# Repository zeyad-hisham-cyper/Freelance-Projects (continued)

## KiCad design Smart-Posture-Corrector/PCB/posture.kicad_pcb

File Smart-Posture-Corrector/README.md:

# Smart Posture Corrector — "Second Spine"

**A two-board wearable that watches your back and neck angle with two IMUs, buzzes you when you slouch, and streams live posture data to a Flutter companion app over Bluetooth Low Energy.**

ESP32 · 2× MPU-6050 · complementary filter · haptic feedback · BLE GATT · Flutter · KiCad 9 · 1S Li-Po with TP4056 charging and MT3608 boost

---

## Overview

The project began with a client specification (`Smart Posture Corrector.docx`) for a wearable aimed at **doctors and dentists**. These users spend long hours in strained working postures. The device needed to:

- monitor the **upper back (thoracic)** and **neck (cervical)** separately, and interpret the neck *relative to* the back ("sensor coherence")
- give a **gentle, location-specific vibration** when posture leaves the calibrated envelope
- **calibrate** to the user's normal working posture, then **tighten the threshold progressively** (adaptive correction, e.g. 30° → 25° → 20°)
- provide a **Special mode** for procedures that need an awkward posture. This mode mutes alerts but still gives a periodic "take a break" reminder.
- be controllable from a **button on the device** and from a **companion mobile app**

This repository contains the full implementation:

| Part | Folder | What it is |
|---|---|---|
| Firmware | [`main/posture controller/`](main/posture%20controller/) | PlatformIO / Arduino-ESP32 firmware (modular C++) |
| Mobile app | [`second_spine/`](second_spine/) | Flutter app "Second Spine" (BLE dashboard, controls, history) |
| Hardware | [`PCB/`](PCB/) | KiCad 9 project: Back board (main) + Neck board, plus Gerbers |
| Docs | [`docs/`](docs/) | Exported schematics (PDF/SVG), PCB layout and 3D renders |

> The device is a wellness and ergonomics aid for healthy users, not a medical device. The original specification says the same.

---

## Features

**Device / firmware**
- Two MPU-6050 IMUs on one I²C bus at 400 kHz: **back sensor at `0x68`**, **neck sensor at `0x69`**
- Pitch is estimated at **100 Hz** with a **complementary filter** (α = 0.96, gyro ±250 °/s)
- The neck angle is reported **relative to the back** (`neck − back`), so leaning the whole torso is not counted as a neck fault
- **Calibration** averages the user's posture over 2 minutes. The baseline and sensitivity level are stored in flash (EEPROM emulation) and survive power cycles.
- **6 sensitivity levels (0–5).** Each level tightens the threshold by 5°, with floors of 15° (back) and 10° (neck).
- **Two-stage, location-specific haptics:** a double buzz after 3 s of bad posture and a triple buzz after 15 s. Only the offending zone's motor (back or neck) vibrates.
- **Special mode:** posture alerts are muted and both motors give a short reminder buzz every 5 minutes
- **One-button UI:** a short press toggles Special mode and a long press (≥ 1.5 s) re-calibrates
- **BLE GATT server** (`PostureCorrector`): JSON telemetry at about 5 Hz plus a text command channel. Advertising restarts automatically after a disconnect.
- A serial debug console accepts single-key commands

**Companion app (Second Spine)**
- BLE scan and connect with Android 12+ runtime permissions
- Live dashboard: Good/Bad status, back and neck arc gauges against their thresholds, and per-zone hints
- Remote **Calibrate**, **Normal ↔ Special** toggle and **sensitivity slider**. The level is saved locally and re-sent on every connect.
- History screen with a posture-trend chart (fl_chart) and session cards (see the [status](#roadmap--status) note below)
- Dark "glass" UI theme using the Outfit font (Google Fonts), locked to portrait

**Hardware**
- Two custom PCBs connected by a 6-wire cable (3V3, GND, SCL, SDA, neck-motor drive, battery rail)
- 1S Li-Po → TP4056 charger module → slide power switch → MT3608 boost (5 V) → ESP32-DevKitC (on-board 3V3 LDO)
- Coin vibration motors on low-side NPN drivers with flyback diodes
- Through-hole (THT) design routed on the bottom copper layer only (see [PCB manufacturing](#pcb-manufacturing))

---

## System architecture

```mermaid
flowchart LR
    subgraph NECK["Neck board"]
        IMU2["GY-521<br/>MPU-6050 @0x69"]
        DRV2["NPN driver<br/>+ flyback diode"]
        M2(("Neck<br/>coin motor"))
        DRV2 --> M2
    end

    subgraph BACK["Back board (main)"]
        IMU1["GY-87<br/>MPU-6050 @0x68"]
        ESP["ESP32-DevKitC-32E<br/>PostureApp firmware"]
        BTN["Push button<br/>GPIO16"]
        DRV1["NPN driver<br/>+ flyback diode"]
        M1(("Back<br/>coin motor"))
        PWR["1S Li-Po → TP4056<br/>→ switch → MT3608 5 V"]
        DRV1 --> M1
    end

    IMU1 -- "I²C 400 kHz" --> ESP
    IMU2 -- "I²C over 6-pin JST cable" --> ESP
    BTN --> ESP
    ESP -- "GPIO25 (VM2)" --> DRV1
    ESP -- "GPIO17 (VM1) over cable" --> DRV2
    PWR -- "5 V → DevKit LDO → 3V3" --> ESP

    ESP <-- "BLE GATT<br/>JSON notify @5 Hz / text commands" --> APP["📱 Second Spine<br/>Flutter app"]
    APP --> SP[("SharedPreferences<br/>level · device id · sessions")]
```

Data flow: **IMUs → complementary filter → back angle and neck-relative angle → threshold logic → vibration events**. In parallel, **angles, thresholds and mode → JSON → BLE notify → app UI**.

---

## Hardware

Two boards share one KiCad project (`PCB/posture.kicad_pro`). The v2 layout places both outlines on one panel. The silkscreen reads *"Back Board"*, *"Smart Posture V 0.3"* and *"Second Spine"*.

| Board | Outline (from `posture.kicad_pcb`) | Contents |
|---|---|---|
| **Back board (main)** | ≈ 98 × 65 mm | ESP32-DevKitC-32E, GY-87 IMU (back sensor), TP4056 and MT3608 module footprints, Li-Po JST, slide switch, push button, back motor driver and JST, 6-pin cable connector, bulk capacitors |
| **Neck board** | ≈ 31 × 44 mm | GY-521 IMU (neck sensor, AD0 pulled up → `0x69`), neck motor driver and JST, 6-pin cable connector |

There is also a standalone neck schematic at `PCB/neck/neck.kicad_sch` with the same circuit. No separate `neck.kicad_pcb` file exists in the repo. The neck layout lives in the combined `posture.kicad_pcb`, and the older standalone neck board survives only as Gerbers (`PCB/Board2/`).

### BOM highlights (from the schematic)

| Ref | Part | Role |
|---|---|---|
| U1 | ESP32-DevKitC-32E (module footprint) | MCU, BLE radio, USB programming |
| U3 | GY-87 10-DOF breakout (MPU-6050 + extras) | Back IMU, `0x68`. Only the MPU-6050 is used by the firmware. |
| U2 | GY-521 breakout (MPU-6050) | Neck IMU, `0x69` (R3 4.7 kΩ pulls AD0 to 3V3) |
| — | TP4056 module (J3/J11 headers) | 1S Li-Po charging (B+/B−, OUT+/OUT−) |
| — | MT3608 module (J5–J8 pins) | Boost converter, battery → +5 V for the DevKit |
| SW2 | SPDT slide switch | Main power (TP4056 OUT+ → MT3608 VIN+) |
| SW1 | Tactile push button | Mode / calibrate (GPIO16, internal pull-up) |
| Q1, Q2 | NPN BJT, TO-92 | Low-side vibration-motor switches |
| R2, R4 / R1, R5 | 470 Ω / 10 kΩ | Base resistor / base pull-down |
| D1, D3 | 1N4001 | Motor flyback diodes |
| J4, J10 | 2-pin JST | Coin vibration motors (neck / back) |
| J9 | 2-pin JST | 1S Li-Po battery |
| J1, J2 | 6-pin JST (locking) | Back ↔ Neck board cable |
| C3, C4 | 100 nF + 10 µF | +5 V decoupling |

Third-party symbols, footprints and 3D models (GY-521, GY-87, a C0720B001F coin-motor footprint) are in `PCB/lib/` and `PCB/GY-521.pretty/`. They were downloaded from SnapEDA.

### Pin map (ESP32-DevKitC-32E)

| Signal | GPIO | Net | Notes |
|---|---|---|---|
| I²C SDA | 21 | `SDA` | Shared by both IMUs and routed to the neck board |
| I²C SCL | 22 | `SCL` | 400 kHz |
| Back motor | 25 | `VM2` | Q1 → J10 (back board) |
| Neck motor | 17 | `VM1` | Sent over the cable → neck-board driver → neck motor |
| Button | 16 | `IO16` | Active-low, `INPUT_PULLUP`, 40 ms debounce |
| 5 V in | 5V pin | `+5V` | From MT3608 |
| 3V3 | 3V3 pin | `+3.3V` | DevKit LDO output → IMUs |

The firmware pins (`src/PostureApp.cpp`) match the v2 netlist.

**Inter-board cable (J1/J2, 6-pin):** `1 +3.3V · 2 GND · 3 SCL · 4 SDA · 5 VM1 · 6 3.7V`

### Power path

```
1S Li-Po (J9) ──► TP4056 module (charge + B−) ──OUT+──► SW2 ──► MT3608 boost ──► +5V ──► ESP32-DevKitC 5V pin
      │                                                                                     └─ on-board LDO ─► +3.3V ─► IMUs
      └──── "3.7V" rail (battery +) ──► coin motors (high side) ◄── NPN low-side switch ◄── GPIO
```

Inference from the netlist: the motors run directly from the battery rail and are switched on the low side. They draw nothing while the ESP32 is off, because the transistors are held off by the 10 kΩ base pull-downs. The design does not include battery-voltage sensing.

Schematics: [main board PDF](docs/main_board_schematic.pdf) · [neck board PDF](docs/neck_board_schematic.pdf)

---

## Firmware

PlatformIO project, `env:esp32dev` (Arduino framework, `espressif32`), 115200 baud monitor, 921600 baud upload.

### Module structure

```
posture controller/
├── src/main.cpp              → setup()/loop(), creates PostureApp
├── src/PostureApp.cpp        → app state machine, pins, button/serial/BLE wiring
├── include/PostureApp.h
├── lib/Sensors/              → raw MPU-6050 I²C reads + complementary filter
├── lib/PostureLogic/         → calibration, thresholds, bad-posture timing, EEPROM persistence
├── lib/Hardware/button.*     → debounced short/long press detector
├── lib/Hardware/vibrationCoin.* → non-blocking vibration patterns
├── lib/BLEDashboard/         → BLE GATT server (ESP32 BLE Arduino)
└── test/test_logic.cpp       → Unity tests for PostureLogic (see status)
```

Everything is **non-blocking** and driven by `millis()`. The main loop updates the button, sensors, motors and BLE every iteration.

### Posture algorithm

1. **Sensing (100 Hz).** For each MPU-6050, read 14 bytes from `0x3B`.
   - Accelerometer pitch: `atan2(−ax, √(ay² + az²))`
   - Gyro rate: `gy / 131` °/s
   - Fusion: `angle = 0.96·(angle + gyro·dt) + 0.04·accel_pitch`
2. **Neck coherence.** `neckRel = neckAngle − backAngle`
3. **Calibration (2 min).** The firmware averages `back` and `neckRel` to get the baseline, resets the level to 0 and saves the result to flash. The firmware comment marks the 2-minute duration as "for testing". The spec suggests 15–30 min or longer.
4. **Threshold.** `th = baseline − 5° × level`, clamped to **≥ 15° (back)** and **≥ 10° (neck)**.
5. **Detection.** Posture is bad when `|back| > backTh` **or** `|neckRel| > neckTh`.
   - Bad for 3 s → `FIRST_BAD` → double buzz
   - Bad for 15 s → `PERSISTENT_BAD` → triple buzz
   - Further alerts stop until posture recovers
   - Only the motor for the offending zone fires

**Flash layout (64-byte EEPROM emulation):** magic `0x504F5354` ("POST") @0, level @4, baseline back (float) @8, baseline neck (float) @12.

### State machine

```mermaid
stateDiagram-v2
    [*] --> CALIBRATING: no valid baseline in flash
    [*] --> NORMAL: baseline loaded
    CALIBRATING --> NORMAL: 2 min elapsed → save baseline, triple buzz (both motors)
    NORMAL --> SPECIAL: short press / TOGGLE_MODE (double buzz)
    SPECIAL --> NORMAL: short press / TOGGLE_MODE (short buzz)
    NORMAL --> CALIBRATING: long press ≥1.5 s / CALIBRATE
    SPECIAL --> CALIBRATING: long press ≥1.5 s / CALIBRATE
    CALIBRATING --> CALIBRATING: long press / CALIBRATE (restart)

    state NORMAL {
        [*] --> Good
        Good --> Bad: angle > threshold
        Bad --> Good: posture corrected
        Bad --> Warned: 3 s → double buzz
        Warned --> Persistent: 15 s → triple buzz
        Warned --> Good
        Persistent --> Good
    }
    note right of SPECIAL: alerts muted, short reminder buzz every 5 min
```

### Vibration patterns

| Pattern | Timing | Used for |
|---|---|---|
| Short | 200 ms | Leaving Special mode, 5-min Special reminder |
| Double | 2 × (200 ms on / 150 ms off) | Entering Special mode, first bad-posture warning |
| Triple | 3 × (200 ms on / 150 ms off) | Calibration done, persistent bad posture |

### BLE protocol

Device name **`PostureCorrector`**. The service UUID is advertised with a scan response enabled.

| Item | UUID | Properties | Payload |
|---|---|---|---|
| Service | `12345678-1234-1234-1234-123456789abc` | — | — |
| Posture data | `12345678-1234-1234-1234-000000000001` | Read, Notify | JSON, about every 200 ms while connected |
| Command | `12345678-1234-1234-1234-000000000002` | Write | UTF-8 text command |
| Status | `12345678-1234-1234-1234-000000000003` | Read | `"CALIBRATING"` / `"NORMAL"` / `"SPECIAL"` |

**Notify payload:**

```json
{"back":12.50,"neck":-3.20,"backTh":15.0,"neckTh":10.0,"mode":1,"calibrating":false}
```

`mode`: `0` Calibrating, `1` Normal, `2` Special. `back` is in degrees and `neck` is the neck-relative angle.

**Commands:**

| Command | Effect |
|---|---|
| `CALIBRATE` | Start a 2-minute calibration |
| `TOGGLE_MODE` | Normal ↔ Special (ignored while calibrating) |
| `LEVEL:n` | Set sensitivity level `n` = 0–5 (values above 5 are clamped). Saved to flash. |

**Serial console (115200 baud):** `c` calibrate · `s` toggle Special · `n` force Normal · `0`–`5` set level. The device prints `[APP] Mode=… | Back=… | Neck=…` once per second.

---

## Mobile app — Second Spine

Flutter (Dart SDK `^3.10.4`), dark theme, portrait only. It has three tabs:

| Tab | Screen | What it does |
|---|---|---|
| Dashboard | `home_screen.dart` | Connection chip, Good/Bad status card (pulses when bad), calibrating spinner, back and neck `AngleGauge`s, Calibrate and Mode buttons, sensitivity slider (0–5) with live `±backTh / ±neckTh` |
| Connect | `connect_screen.dart` | Radar-style 15 s BLE scan, device list with RSSI, connect/disconnect. On connect it stores the device id and re-sends the saved `LEVEL:n`. |
| History | `history_screen.dart` | Posture-trend line chart (last 10 sessions) and session cards (duration, % good posture, Good ≥ 70 %) |

**Architecture:** `BleService` (a `ChangeNotifier` around `flutter_blue_plus` that exposes a `PostureData` stream) and `StorageService` (`shared_preferences` keys `sensitivity_level`, `last_device_id`, `session_history`, keeping at most 50 sessions).

**Packages** (`pubspec.yaml`): `flutter_blue_plus ^1.35.5`, `permission_handler ^12.0.1`, `shared_preferences ^2.3.4`, `fl_chart ^0.70.2`, `google_fonts ^6.2.1`, `cupertino_icons`. Dev: `flutter_lints ^6.0.0`.

See [`second_spine/README.md`](second_spine/README.md) for details.

---

## Build & flash the firmware

Requires [PlatformIO](https://platformio.org/) (CLI or the VS Code extension).

```bash
cd "main/posture controller"
pio run                         # build
pio run -t upload               # flash the ESP32-DevKitC over USB
pio device monitor -b 115200    # serial console (c / s / n / 0-5)
```

On first boot the device has no baseline, so it **starts calibrating immediately**. Sit or stand in your normal working posture for 2 minutes and wait for the triple buzz.

## Run the app

```bash
cd second_spine
flutter pub get
flutter run            # with an Android phone connected (BLE needs a real device)
flutter build apk      # release APK (currently signed with the debug key)
```

Android permissions (`BLUETOOTH_SCAN`, `BLUETOOTH_CONNECT`, and location on Android ≤ 11) are already declared in `AndroidManifest.xml`. iOS has not been configured yet; see the status section.

---

## PCB manufacturing

The design is KiCad 9 (`PCB/posture.kicad_pro`), 1.6 mm FR-4. All tracks (0.5 / 0.8 / 1.0 mm) are on **B.Cu** with a GND pour, and every part is through-hole. Each Gerber set exports bottom copper only (there is no `F_Cu.gbr`). That suits single-sided or home/CNC fabrication, and a fab house can also build it as a 2-layer board with an empty top layer.

| Folder | Date (job file) | Board size | Contents | Status |
|---|---|---|---|---|
| `PCB/Board1/` (+ `Board1.zip`) | 2026-01-13 | 103.8 × 61.9 mm | First back board. No on-board Li-Po JST, power switch or bulk caps; button net differs. | Superseded |
| `PCB/Board2/` (+ `Board2.zip`) | 2026-01-13 | 44.4 × 33.1 mm | First standalone neck board | Superseded |
| **`PCB/v2/`** (+ `v2/v2.zip`) | **2026-03-16** | **133.6 × 65.4 mm panel** | **Back board + neck board on one panel**. Adds Li-Po JST, SW2 power switch, 5 V decoupling and button on GPIO16, and matches the current firmware pin map. | **Current** |

Gerbers were generated with Pcbnew 9.0.2. For ordering, upload `PCB/v2/v2.zip`. It contains two separate outlines, so ask the fab to route or separate them, or order them as a panel.

---

## Gallery

| | |
|---|---|
|  |  |
| 3D render, top | 3D render, bottom (single-sided routing + GND pour) |

**PCB layout:** [`docs/images/main_board/pcb_layout.svg`](docs/images/main_board/pcb_layout.svg)

**Schematics**

| Sheet | File |
|---|---|
| Main board (root) | [`posture.svg`](docs/images/main_board/schematic/posture.svg) |
| TP4056 charger sheet | [`posture-TP4056.svg`](docs/images/main_board/schematic/posture-TP4056.svg) |
| MT3608 boost sheet | [`posture-MT3608.svg`](docs/images/main_board/schematic/posture-MT3608.svg) |
| Neck board | [`neck.svg`](docs/images/neck_board/schematic/neck.svg) |

---

## Repository structure

```
Smart-Posture-Corrector/
├── README.md                         ← you are here
├── Smart Posture Corrector.docx      ← original client specification
├── docs/
│   ├── main_board_schematic.pdf
│   ├── neck_board_schematic.pdf
│   └── images/
│       ├── main_board/   pcb_3d_iso/top/bottom.png, pcb_layout.svg, schematic/*.svg
│       └── neck_board/   schematic/neck.svg
├── main/                             ← firmware repo
│   ├── README.md
│   └── posture controller/           ← PlatformIO project
│       ├── platformio.ini
│       ├── include/  src/  lib/  test/
│       └── README.md                 ← BLE integration guide
├── second_spine/                     ← Flutter companion app
│   ├── pubspec.yaml
│   ├── lib/ (main.dart, models/, screens/, services/, theme/, widgets/)
│   ├── android/ ios/ web/ windows/ linux/ macos/
│   └── README.md
└── PCB/                              ← KiCad 9 project
    ├── posture.kicad_pro/.kicad_sch/.kicad_pcb   (main + neck panel)
    ├── TP4056.kicad_sch  MT3608.kicad_sch        (hierarchical sheets)
    ├── neck/neck.kicad_sch                       (standalone neck schematic)
    ├── GY-521.pretty/  lib/                      (third-party parts, SnapEDA)
    ├── Board1/  Board2/                          (v1 Gerbers)
    └── v2/                                       (current Gerbers)
```

---

## Roadmap / status

Status (from the files): the firmware, BLE protocol, app and v2 PCB are complete and consistent with each other. The items below are open or differ from the original spec.

- [ ] **Automatic weekly threshold tightening.** The level (0–5) is currently set manually from the app or serial console. The spec asks for automatic weekly progression.
- [ ] **Special-mode auto-timeout.** The spec suggests about 30 min. Today Special mode lasts until it is toggled off.
- [ ] **Production calibration time.** Calibration is 2 min (marked "for testing"). It also needs a stillness/validity check.
- [ ] **Session history.** `StorageService.addSession()` exists, but nothing records sessions yet, so the History tab stays empty.
- [ ] **Auto-reconnect.** `last_device_id` is saved but not yet used.
- [ ] **iOS.** `NSBluetoothAlwaysUsageDescription` must be added to `Info.plist` before BLE works on iOS.
- [ ] **Unit tests.** `test/test_logic.cpp` accesses private members, and its expected threshold ignores the 15° floor, so it needs updating before `pio test` passes.
- [ ] **Portability.** Some includes differ in case from the file names (`"Sensors.h"`, `"PostureLogic.h"`). This builds on Windows but will fail on Linux/macOS CI. The `Adafruit MPU6050` dependency and the `I2C_SDA/SCL` build flags are declared but unused.
- [ ] **Hardware ideas.** Battery-voltage sense, the GY-87 magnetometer/barometer (currently unused), and an enclosure / strap mount.

---

**Author:** [@zeyad-hisham-cyper](https://github.com/zeyad-hisham-cyper) — Embedded Systems & PCB Design · Part of the [Freelance Projects](../README.md) portfolio

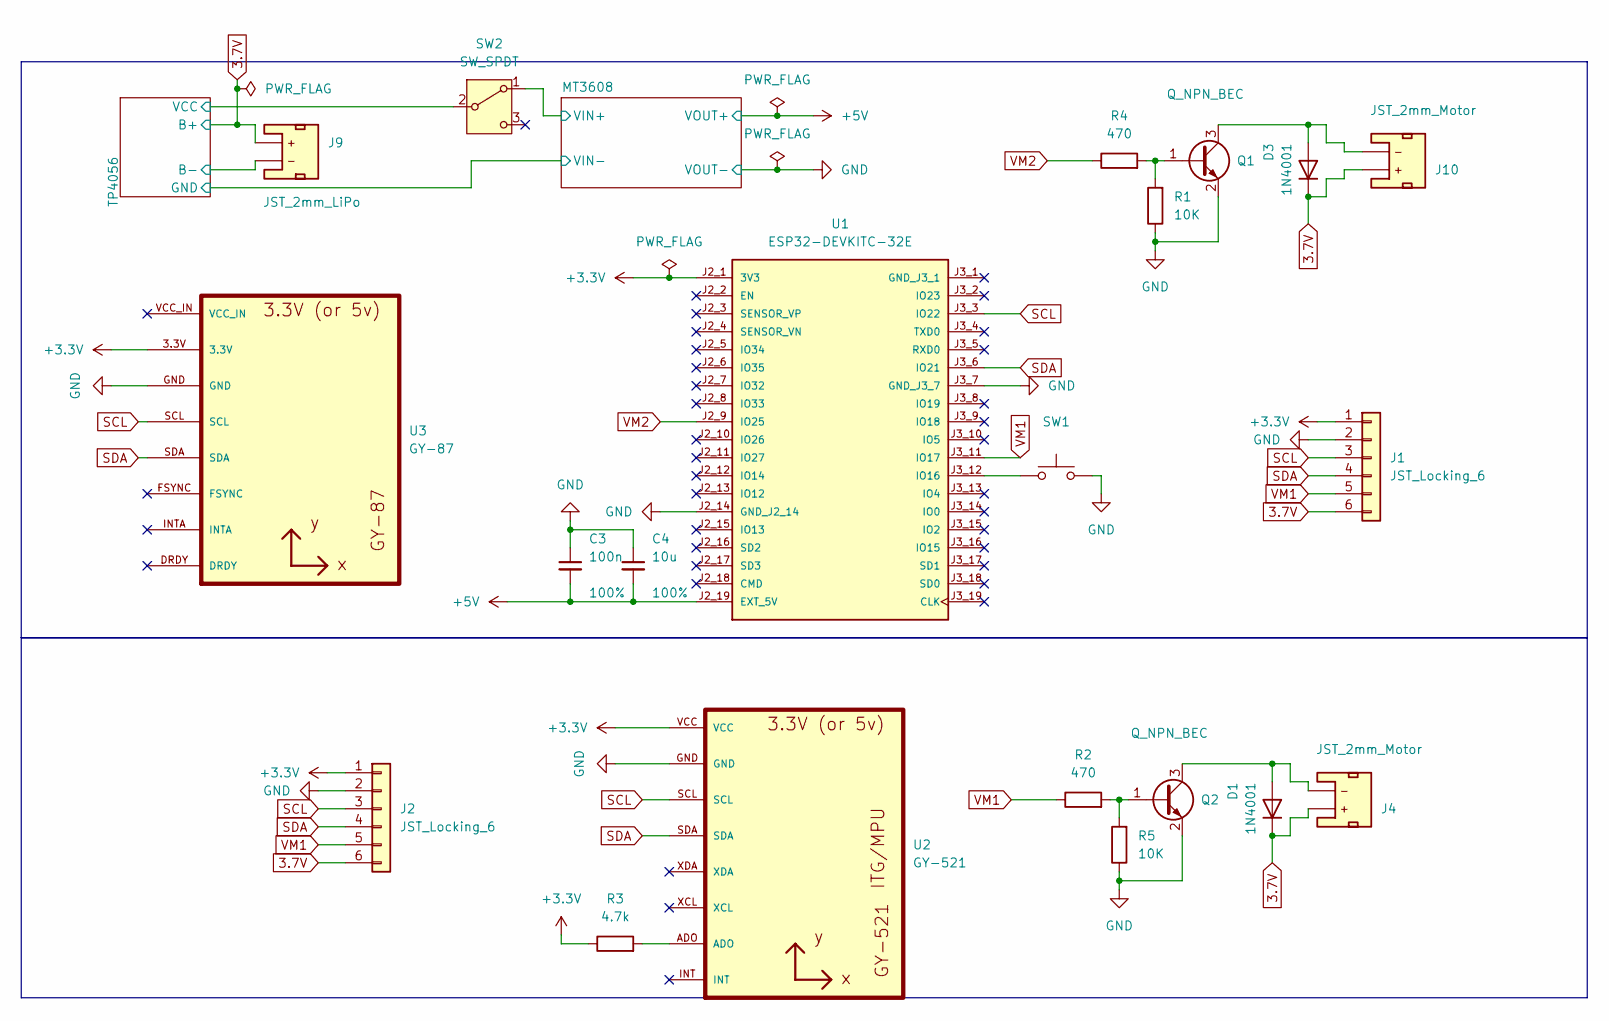
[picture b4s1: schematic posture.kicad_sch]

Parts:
C3: 100n; C_Disc_D5.0mm_W2.5mm_P5.00mm; Voltage 1kV; Tolerance 100%
C4: 10u; C_Radial_D5.0mm_H7.0mm_P2.00mm; Voltage 1kV; Tolerance 100%
D1, D3: 1N4001; D_DO-35_SOD27_P7.62mm_Horizontal
J1, J2: JST_Locking_6; JST_XH_B6B-XH-A_1x06_P2.50mm_Vertical
J4, J10: JST_2mm_Motor; JST_XH_B2B-XH-A_1x02_P2.50mm_Vertical
J9: JST_2mm_LiPo; JST_XH_B2B-XH-A_1x02_P2.50mm_Vertical
Q1, Q2: Q_NPN_BEC; TO-92_Wide
R1, R5: 10K; R_Axial_DIN0207_L6.3mm_D2.5mm_P7.62mm_Horizontal
R2, R4: 470; R_Axial_DIN0207_L6.3mm_D2.5mm_P7.62mm_Horizontal
R3: 4.7k; R_Axial_DIN0207_L6.3mm_D2.5mm_P7.62mm_Horizontal
SW1: PTH_12x12mm_h8.0mm; SW_PUSH_6mm
SW2: SW_SPDT; SW_Slide-03_Wuerth-WS-SLTV_10x2.5x6.4_P2.54mm
U1: ESP32-DEVKITC-32E; MODULE_ESP32-DEVKITC-32E; PARTREV 1.4
U2: GY-521
U3: GY-87

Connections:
3.7V: D1.1 (K), D3.1 (K), J1.6, J2.6, J4.2 (+), J9.2 (+), J10.2 (+); also elsewhere on the board
+3.3V: J1.1, J2.1, R3.1, U1.J2_1 (3V3), U2.VCC, U3.3.3V
+5V: C3.2, C4.2, U1.J2_19 (EXT_5V); also elsewhere on the board
/MT3608/VIN+: SW2.1 (A); also elsewhere on the board
/TP4056/B-: J9.1 (-); also elsewhere on the board
/TP4056/VCC: SW2.2 (B); also elsewhere on the board
GND: C3.1, C4.1, J1.2, J2.2, Q1.2 (E), Q2.2 (E), R1.1, R5.1, SW1.2, U1.J2_14 (GND_J2_14), U1.J3_7 (GND_J3_7), U2.GND, U3.GND; also elsewhere on the board
unnamed: D1.2 (A), J4.1 (-), Q2.3 (C)
unnamed: D3.2 (A), J10.1 (-), Q1.3 (C)
unnamed: Q1.1 (B), R1.2, R4.2
unnamed: Q2.1 (B), R2.2, R5.2
unnamed: R3.2, U2.ADO
unnamed: SW1.1, U1.J3_12 (IO16)
SCL: J1.3, J2.3, U1.J3_3 (IO22), U2.SCL, U3.SCL
SDA: J1.4, J2.4, U1.J3_6 (IO21), U2.SDA, U3.SDA
VM1: J1.5, J2.5, R2.1, U1.J3_11 (IO17)
VM2: R4.1, U1.J2_9 (IO25)

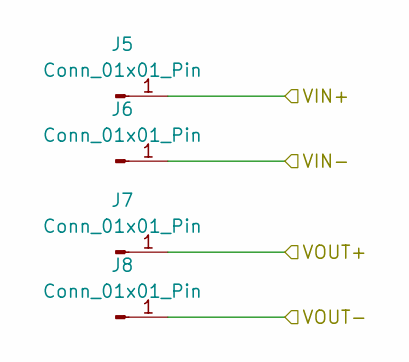
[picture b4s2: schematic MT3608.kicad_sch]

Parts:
J5, J6, J7, J8: Conn_01x01_Pin; PinHeader_1x01_P2.54mm_Vertical

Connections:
+5V: J7.1; also elsewhere on the board
/MT3608/VIN+: J5.1; also elsewhere on the board
/MT3608/VIN-: J6.1; also elsewhere on the board
GND: J8.1; also elsewhere on the board

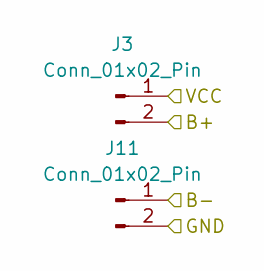
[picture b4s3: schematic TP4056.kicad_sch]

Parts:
J3, J11: Conn_01x02_Pin; PinHeader_1x02_P2.54mm_Vertical

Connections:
3.7V: J3.2; also elsewhere on the board
/MT3608/VIN-: J11.2; also elsewhere on the board
/TP4056/B-: J11.1; also elsewhere on the board
/TP4056/VCC: J3.1; also elsewhere on the board

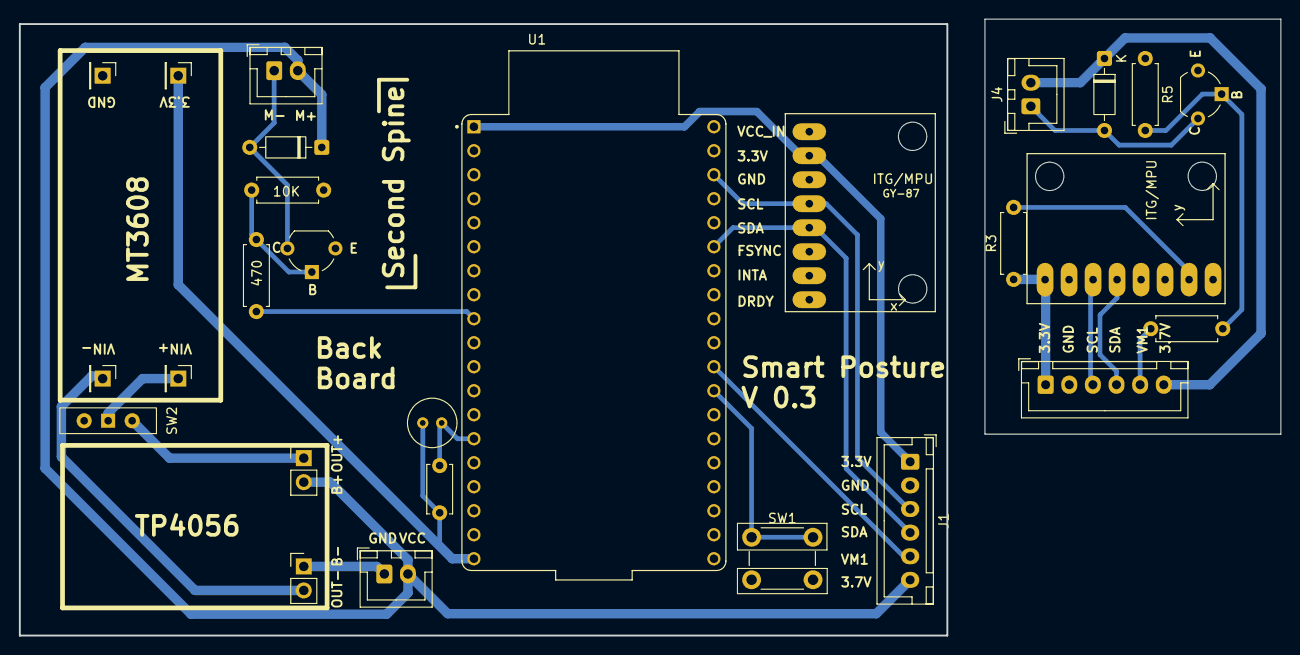
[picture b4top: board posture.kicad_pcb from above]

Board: 2 copper layers, 133.5 x 65.2 mm, 27 parts (0 on the bottom side), 18 nets.
